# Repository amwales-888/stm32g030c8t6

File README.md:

# stm32g030c8t6
Simple breakout board for stm32g030c8t6

- 3.3v LDO powered from 5V USB.
- UART connectivity to USB via ch340 optionally connected to pins PA9/PA10 using jumpers.
- ARM SWD programming interface header.
- All other pins are broken out to headers.
- 1 LEDS optionally connected to pin PB0 using jumper.
- 1 Button with pulldown optionally connected to pin PB1 using jumper.
- 1 Button connected to RESET pin, pulled high.

<table>
  <tr>
    <td> </td>
  </tr>
  <tr>
    <td> </td>
  </tr>
</table>

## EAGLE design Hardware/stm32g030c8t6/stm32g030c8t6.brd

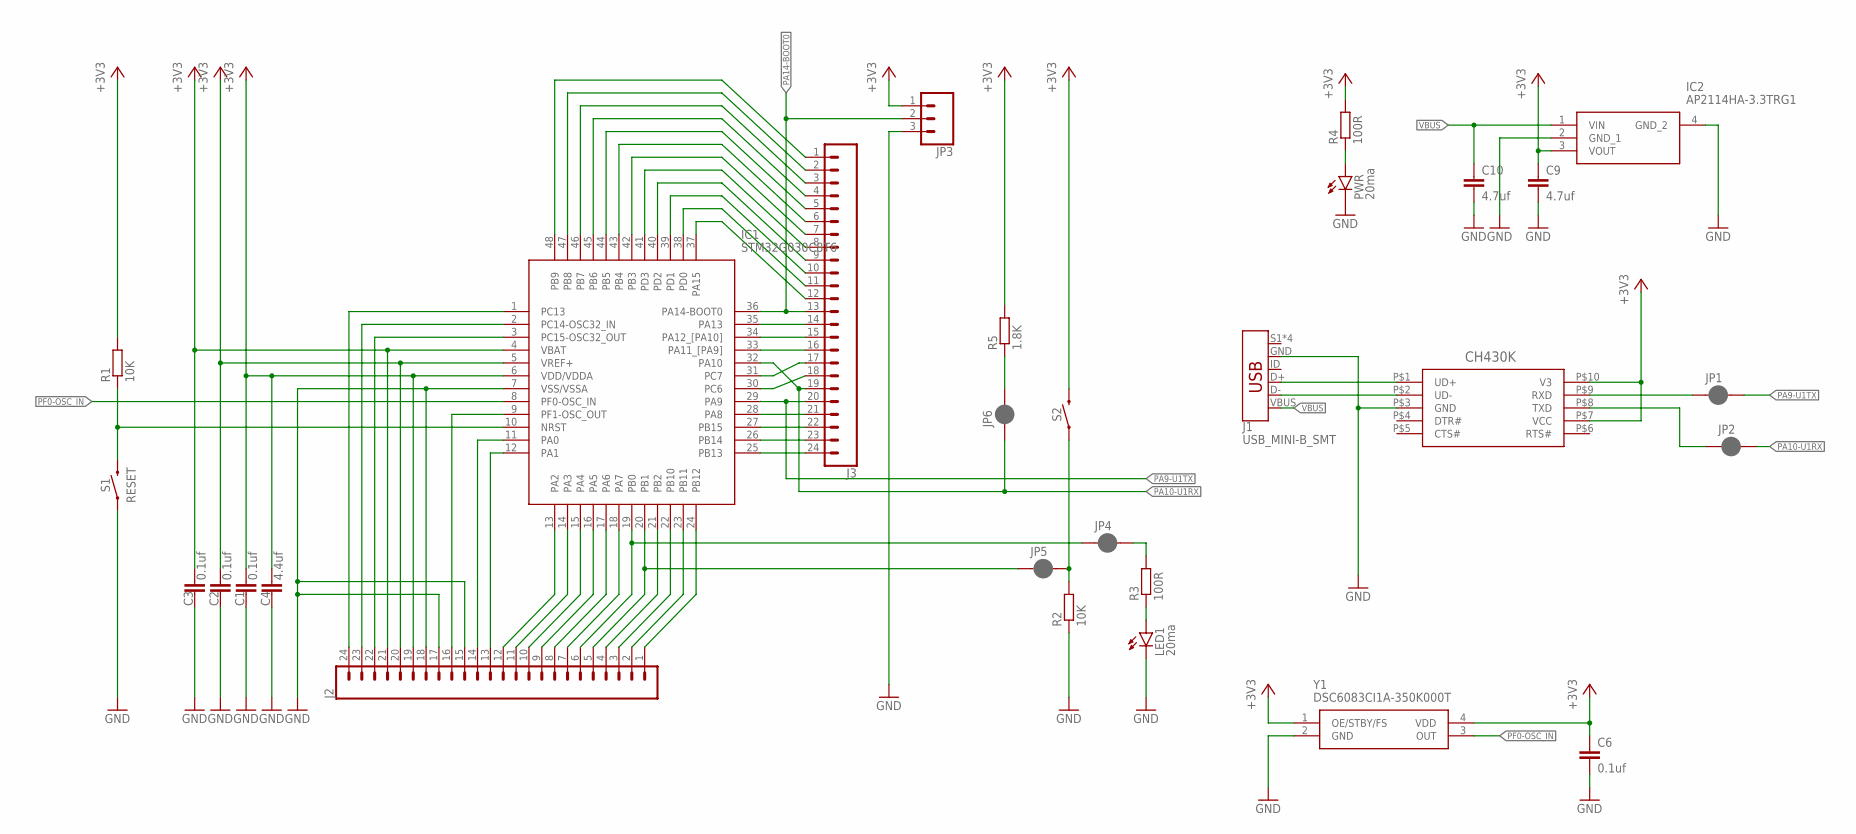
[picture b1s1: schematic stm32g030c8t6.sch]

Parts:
C1, C2, C3, C6: 0.1uf; C0805
C4: 4.4uf; C0805
C9, C10: 4.7uf; C1206
IC1: STM32G030C8T6; QFP50P900X900X160-48N
IC2: AP2114HA-3.3TRG1; SOT230P700X180-4N
J1: USB_MINI-B_SMT; USB-MINIB
J2, J3: CONN_24; 1X24
JP1, JP2, JP4, JP5, JP6: JUMPER-SMT_2_NC_PASTE_SILK; SMT-JUMPER_2_NC_PASTE_SILK
JP3: 455-1750-1-ND; 1X03
LED1: 20ma; SML0805
PWR: 20ma; SML0805
R1, R2: 10K; R0805
R3, R4: 100R; R0805
R5: 1.8K; R0805
S1, S2: RESET; TACTILE_SWITCH_SMD_6.0X3.5MM
U$1: CH430K; ESSOP-10
Y1: DSC6083CI1A-350K000T; DSC6083CI1A350K000T

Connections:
+3V3: C1.1, C2.1, C3.1, C4.1, C6.1, C9.1, IC1.4 (VBAT), IC1.5 (VREF+), IC1.6 (VDD/VDDA), IC2.3 (VOUT), J2.19, J2.20, J2.21, JP3.1, R1.2, R4.2, R5.2, S2.2, U$1.P$7 (VCC), U$1.P$10 (V3), Y1.1 (OE/STBY/FS), Y1.4 (VDD)
A0: IC1.11 (PA0), J2.14
A1: IC1.12 (PA1), J2.13
A2: IC1.13 (PA2), J2.12
A3: IC1.14 (PA3), J2.11
A4: IC1.15 (PA4), J2.10
A5: IC1.16 (PA5), J2.9
A6: IC1.17 (PA6), J2.8
A7: IC1.18 (PA7), J2.7
B0: IC1.19 (PB0), J2.6, JP4.1
B1: IC1.20 (PB1), J2.5, JP5.1
B2: IC1.21 (PB2), J2.4
B10: IC1.22 (PB10), J2.3
B11: IC1.23 (PB11), J2.2
B12: IC1.24 (PB12), J2.1
GND: C1.2, C2.2, C3.2, C4.2, C6.2, C9.2, C10.2, IC1.7 (VSS/VSSA), IC2.2 (GND_1), IC2.4 (GND_2), J1.GND, J2.15, J2.17, J2.18, JP3.3, LED1.C, PWR.C, R2.1, S1.1, U$1.P$3 (GND), Y1.2 (GND)
unnamed: JP6.2, R5.1
unnamed: LED1.A, R3.1
unnamed: JP4.2, R3.2
unnamed: JP5.2, R2.2, S2.1
unnamed: PWR.A, R4.1
PA8: IC1.28 (PA8), J3.21
PA9-U1TX: IC1.29 (PA9), J3.20, JP1.2
PA10-U1RX: IC1.32 (PA10), J3.19, JP2.2, JP6.1
PA11: IC1.33 (PA11_[PA9]), J3.16
PA12: IC1.34 (PA12_[PA10]), J3.15
PA13: IC1.35 (PA13), J3.14
PA14-BOOT0: IC1.36 (PA14-BOOT0), J3.13, JP3.2
PA15: IC1.37 (PA15), J3.12
PB3: IC1.42 (PB3), J3.7
PB4: IC1.43 (PB4), J3.6
PB5: IC1.44 (PB5), J3.5
PB6: IC1.45 (PB6), J3.4
PB7: IC1.46 (PB7), J3.3
PB8: IC1.47 (PB8), J3.2
PB9: IC1.48 (PB9), J3.1
PB13: IC1.25 (PB13), J3.24
PB14: IC1.26 (PB14), J3.23
PB15: IC1.27 (PB15), J3.22
PC6: IC1.30 (PC6), J3.18
PC7: IC1.31 (PC7), J3.17
PC13: IC1.1 (PC13), J2.24
PC14: IC1.2 (PC14-OSC32_IN), J2.23
PC15: IC1.3 (PC15-OSC32_OUT), J2.22
PD0: IC1.38 (PD0), J3.11
PD1: IC1.39 (PD1), J3.10
PD2: IC1.40 (PD2), J3.9
PD3: IC1.41 (PD3), J3.8
PF0-OSC_IN: IC1.8 (PF0-OSC_IN), Y1.3 (OUT)
PF1: IC1.9 (PF1-OSC_OUT), J2.16
PF2-NRST: IC1.10 (NRST), R1.1, S1.2
RXD: JP1.1, U$1.P$9 (RXD)
TXD: JP2.1, U$1.P$8 (TXD)
USB_N: J1.D-, U$1.P$2 (UD-)
USB_P: J1.D+, U$1.P$1 (UD+)
VBUS: C10.1, IC2.1 (VIN), J1.VBUS

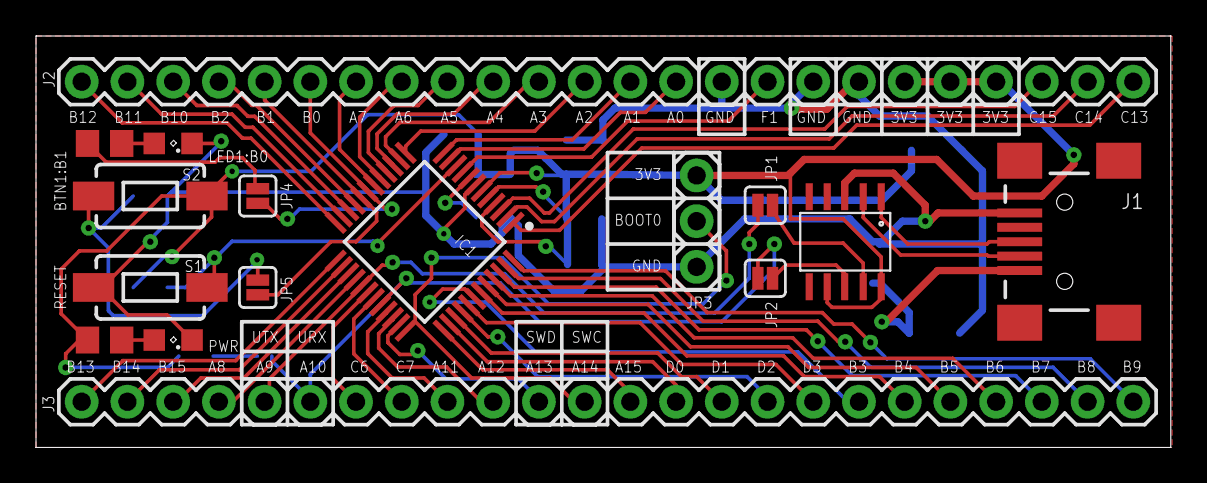
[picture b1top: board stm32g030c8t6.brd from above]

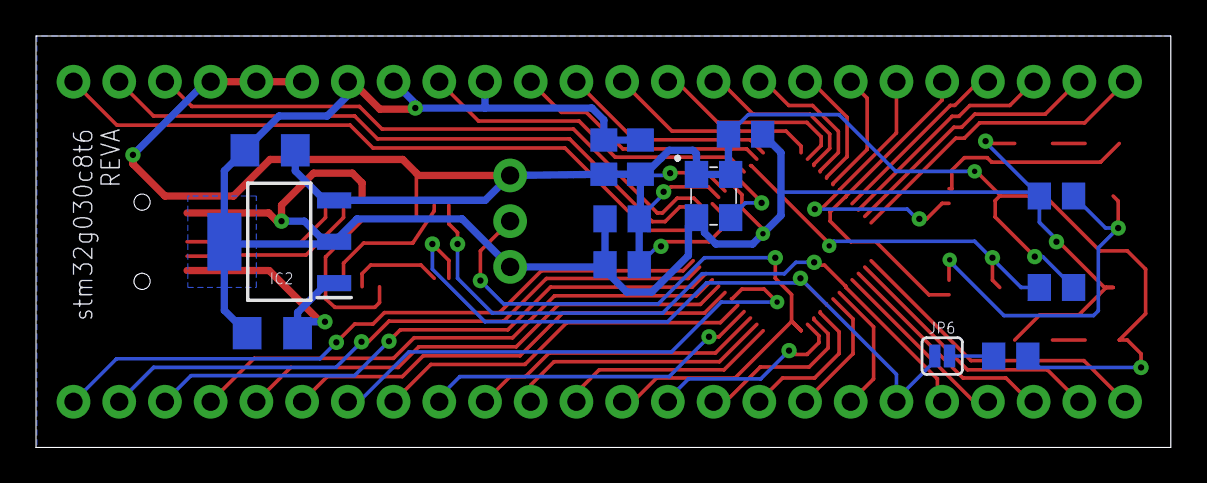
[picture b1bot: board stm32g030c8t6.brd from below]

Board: 2 copper layers, 63.0 x 22.9 mm, 29 parts (13 on the bottom side), 56 nets.

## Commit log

2024-10-29 Initial checkin
2025-01-15 Added pullup to RX pin
2025-01-15 associated bord/schematic with eagle project
2025-01-15 Tidyup schematic, silkscreen, regenerate gerbers and images

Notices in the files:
parts and their libraries:
SparkFun-Connectors: Licensing: Creative Commons ShareAlike 4.0 International - https://creativecommons.org/licenses/by-sa/4.0
